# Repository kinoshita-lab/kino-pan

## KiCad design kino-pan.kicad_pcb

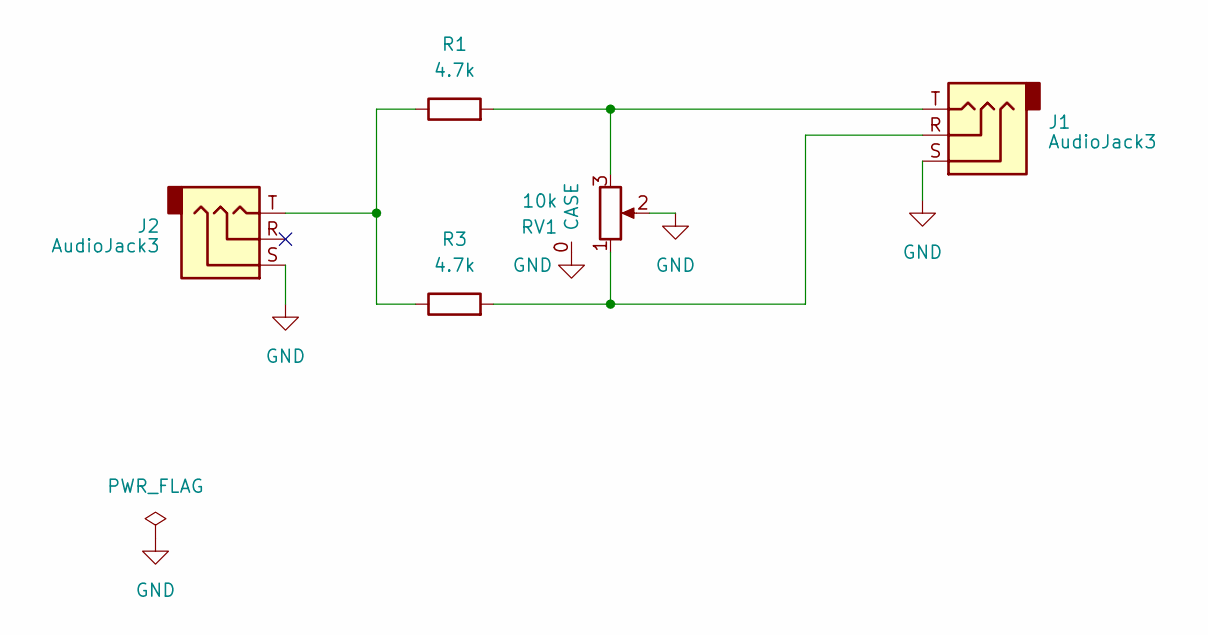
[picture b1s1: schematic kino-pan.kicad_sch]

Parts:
J1, J2: AudioJack3; 3.5mm_Stereo_TRS_PJ-3210-4A_and_ST-005-G; LCSC C136686
R1, R3: 4.7k; R_0402_1005Metric; LCSC C25900
RV1: 10k; Potentiometer_Alps_RK09K_Horizontal_CORRECTED; LCSC C209779

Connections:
GND: J1.S, J2.S, RV1.0 (CASE), RV1.2
unnamed: J1.R, R3.2, RV1.1
unnamed: J1.T, R1.2, RV1.3
unnamed: J2.T, R1.1, R3.1

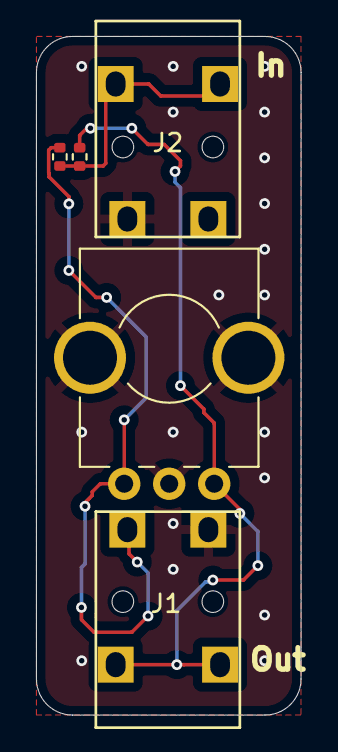
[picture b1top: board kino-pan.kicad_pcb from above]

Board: 2 copper layers, 14.7 x 37.7 mm, 5 parts (0 on the bottom side), 4 nets.

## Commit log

2025-03-17 initial
2025-03-17 add pdf documents
2025-03-17 add readme
